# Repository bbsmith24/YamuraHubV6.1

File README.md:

## YamuraLog Hub
Control for YamuraLog sensor network. Start/Stop logging, save log file to microSD, handle FTP communications with data viewer

## Hardware
- Teensy 4.1. Log files go to its built-in microSD slot (4-bit SDIO, `SD.begin(BUILTIN_SDCARD)`), not the display's SD slot.
- Waveshare SN65HVD230 CAN tranciever
- Hosyond 4" 320x480 display (with built in microSD card slot)
- Adafruit Airlift

## Required Libraries
This is a Visual Code/Platform IO project, I don't recommend using Arduino IDE for this, although the code did start there.
Install these libraries:

- `WiFiNINA - Adafruit fork`
- `SPI`
- 'TFT_eSPI'
- 'FlexCan_T4'
- 'ArduinoJson'

## Usage

1. Open `WiFiSecrets.h`.
2. Replace the WiFi credentials:
   - `YOUR_SSID`
   - `YOUR_WIFI_PASSWORD`
3. Replace the FTP server details:
   - `FTP_SERVER`
   - `FTP_USER`
   - `FTP_PASS`
   - 'FTP_PATH'
4. Adjust pin definitions in main.h as needed:
5. Build and upload to Teensy 4.1.
6. For full debug messages, uncomment #define DEBUG_EXTRA_VERBOSE. Use #define DEBUG_VERBOSE for more serious(?) messages
7. Open Serial Monitor at `115200` baud.

## Configuration (SD `config.ini`)

The values in `WiFiSecrets.h` are compiled-in **defaults**. If a `config.ini`
file is present at the top level of the SD card, its fields override those
defaults at boot, and its `[drivers]` section fills the Select Driver menu.
Copy `config.ini.sample` to the card as `config.ini` and edit it. Any field you
omit keeps its compiled default. This keeps real credentials off committed
source. See `Config.h` for the format.

## Notes

- To log anything, you need at least 1 YamuraLog node (GPS, IMU, A/D), appropriate CAN cables and terminators.

## PlatformIO

A `platformio.ini` file is included for Teensy 4.1 builds (`env:teensy41`).

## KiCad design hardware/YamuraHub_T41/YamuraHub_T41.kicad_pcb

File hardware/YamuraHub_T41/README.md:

# YamuraLog Hub carrier board, Teensy 4.1 (rev B)

A 2-layer, all through-hole board, 122 × 68 mm, built in KiCad 10. It carries the same parts as the YamuraHubV6.1 hub, with the Teensy 4.0 replaced by a Teensy 4.1.

**The display goes on the front; every other part goes on the back.**
- **Front:** the 4″ display (MSP4030/4031, 108 × 60.88 mm) plugs into the J4 socket, with its long side along the board. It's held by M3 standoffs at its own four mounting holes (H5–H8).
- **Back:** the Teensy, AirLift, CAN board, power section, connectors and headers.
- **Board size:** the display outline plus a margin at each end for the four corner mounting holes (H1–H4).

| File | Contents |
|---|---|
| `YamuraHub_T41.kicad_pro / .kicad_sch / .kicad_pcb` | KiCad project, schematic and board |
| `YamuraHub.pretty`, `YamuraHub.kicad_sym` | Project footprint (Teensy 4.1) and symbols |
| `fab/YamuraHub_T41_gerbers.zip` | Gerbers and Excellon drill files, ready to upload to a board house |
| `fab/YamuraHub_T41_BOM.csv` | Bill of materials |
| `docs/` | Schematic PDF, 3D renders (top = display side, bottom = parts side) and layer plots |
| `gen/` | Scripts that generate the whole design from `gen/design.py` (see *Regenerating*) |

## Changes from rev A
- **Two DB9 CAN connectors** (J3, J8), wired in parallel, so the CAN bus can pass through the hub.
- **No on-board buttons or LEDs.** The buttons are panel-mounted and connect to J6. The panel LEDs connect to J7, with their 330 Ω resistors (R1/R2) still on the board.
- **The display plugs straight onto the board** (J4 socket on the front) instead of connecting by cable, and everything else moved to the back.
- **Board size:** 122 × 68 mm, up from 120 × 80 mm, with M3 holes at all four corners.

## What changed from the Teensy 4.0 hub
- **The SD card moved to the Teensy 4.1's built-in microSD slot**, which uses the fast 4-bit SDIO interface. The old SD chip select (pin 3) and the display's SD slot are no longer used, and the display's `SD_CS` pin is left unconnected.
- **The display's SDO (MISO) line is cut off by default with JP1.** The display controller doesn't release its SDO line when it isn't selected, so on a shared MISO line it would interfere with the AirLift. The firmware never reads from the display, so leave JP1 open.

## Pin map (from `src/main.h`)
| Function | Teensy pin |
|---|---|
| SPI: MOSI / MISO / SCK | 11 / 12 / 13 (shared by AirLift and display) |
| AirLift: CS / RESET / BUSY | 5 / 6 / 9 |
| Display: CS / DC (RS) / RST | 15 / 2 / 4 |
| CAN3 (FlexCAN_T4FD): CTX3 / CRX3 | 31 / 30 → SN65HVD230 board |
| Buttons (J6): SELECT / UP / DOWN | 16 / 17 / 18 (to GND, internal pull-ups) |
| LEDs (J7, via R1/R2): recording / GPS | 21 / 22 (330 Ω) |
| I2C (Wire2): SDA2 / SCL2 | 25 / 24 → J5, spare for an on-board GPS |

## Power and CAN
- **J1 power input:** 12 V comes in on J1 and passes through D1 (1N5822, reverse-polarity protection) to the +12 V rail. D4 (1.5KE20A TVS diode) clamps voltage spikes on that rail.
- **5 V supply:** U1 (RECOM R-78E5.0-1.0, a 1 A switching regulator) makes +5 V for the Teensy VIN pin, the AirLift VIN pin, the display VCC pin and the display backlight (LED pin).
- **3.3 V supply:** the Teensy's own 3.3 V output powers the CAN board and J5.
- **J3 and J8 (DB9 male, CAN to the nodes), wired identically:**
  - pin 2 = CAN_L
  - pin 7 = CAN_H
  - pins 3 and 6 = GND
  - pin 9 = +12 V to the nodes, through F1 (1.1 A resettable fuse, shared by both connectors)
  - shell = GND
- **Termination:** the Waveshare SN65HVD230 board has a fixed 120 Ω terminator.
  - **One DB9 used:** the hub is one end of the bus, so leave the terminator in place.
  - **Both DB9s used:** the hub sits mid-bus, so remove the terminator from the Waveshare board, and terminate the two far ends of the bus instead.

## Before ordering, check against your actual parts
1. **AirLift (A2), 12-pin socket**, pin order assumed to be VIN, 3Vo, GND, SCK, MISO, MOSI, CS, BUSY, RST, GP0, RXI, TXO.
2. **Waveshare CAN board (A3), 4-pin socket**, pin order assumed to be 3V3, GND, CTX, CRX. Its CANH/CANL terminals connect to J2 with two short wires.
3. **Display (J4)** follows the MSP4030/4031 14-pin header: VCC, GND, LCD_CS, LCD_RST, LCD_RS, SDI, SCK, LED, SDO, CTP ×4, SD_CS.
4. **Display header position:** J4 assumes the display's header is 2.0 mm in from its left short edge, centred vertically (13.93 mm from top and bottom), with pin 1 (VCC) nearest the bottom edge, front view. These figures come from the MSP4030/4031 outline drawing. Measure your display before ordering; if they're off, the display won't line up with H5–H8.

Each socket's signal names are printed on the silkscreen. If a module's order differs, edit `pins` and `pinnames` for that part in `gen/design.py` and regenerate.

## Assembly notes
- **Cut the Teensy's VUSB-VIN pad** on its underside. Otherwise, with USB plugged in, USB and the board's 5 V supply are tied together.
- **Back-side parts:** solder every part except J4 on the back of the board. Mount the Teensy on female headers, with its USB port at the top edge and its microSD slot at the bottom edge so the card can be swapped.
- **Trim leads under the display:** cut the back-side parts' leads flush on the front. The display's underside (SMD parts up to 2.2 mm, plus its SD slot) sits over them, held at the J4 socket height by the standoffs.
- **Leave JP1 open** (see above).
- **Panel controls:** J6 (SELECT, UP, DOWN, GND) and J7 (REC, GPS, GND) go to the panel buttons and LEDs.

## Firmware
The `teensy41` branch of YamuraHubV6.1 already builds for this board: `env:teensy41`, with `SD.begin(BUILTIN_SDCARD)`. Every other pin is unchanged from the Teensy 4.0 hub.

## Regenerating
Everything in this folder is generated from `gen/design.py`:
```
python gen/build_sch.py                                      # schematic and symbol library
kicad-cli sch export netlist -o gen/out/YamuraHub_T41.net YamuraHub_T41.kicad_sch
"C:/Program Files/KiCad/10.0/bin/python.exe" gen/build_pcb.py  # placement; pad nets come from the netlist
"C:/Program Files/KiCad/10.0/bin/python.exe" gen/route.py      # grid router and GND pours
```
- **Back-side parts:** parts marked `side="B"` in `design.py` are flipped onto the back, and their labels go on the back silkscreen.
- **Routing retries:** the router routes one net at a time. If a net fails, it starts again with the failed nets routed first, for up to 8 attempts.
- **Hand edits:** rebuilding this way discards any hand edits made in KiCad. If you route by hand in KiCad, stop running these scripts.

## Check results (rev B)
- **ERC:** 0 errors, 0 warnings.
- **DRC with schematic parity:** 0 unconnected pads, 0 board/schematic mismatches, and no courtyard or clearance errors.
- **Remaining DRC warnings, not errors:** two ground-pour connections are partial thermal reliefs. Both pads are also connected by tracks.

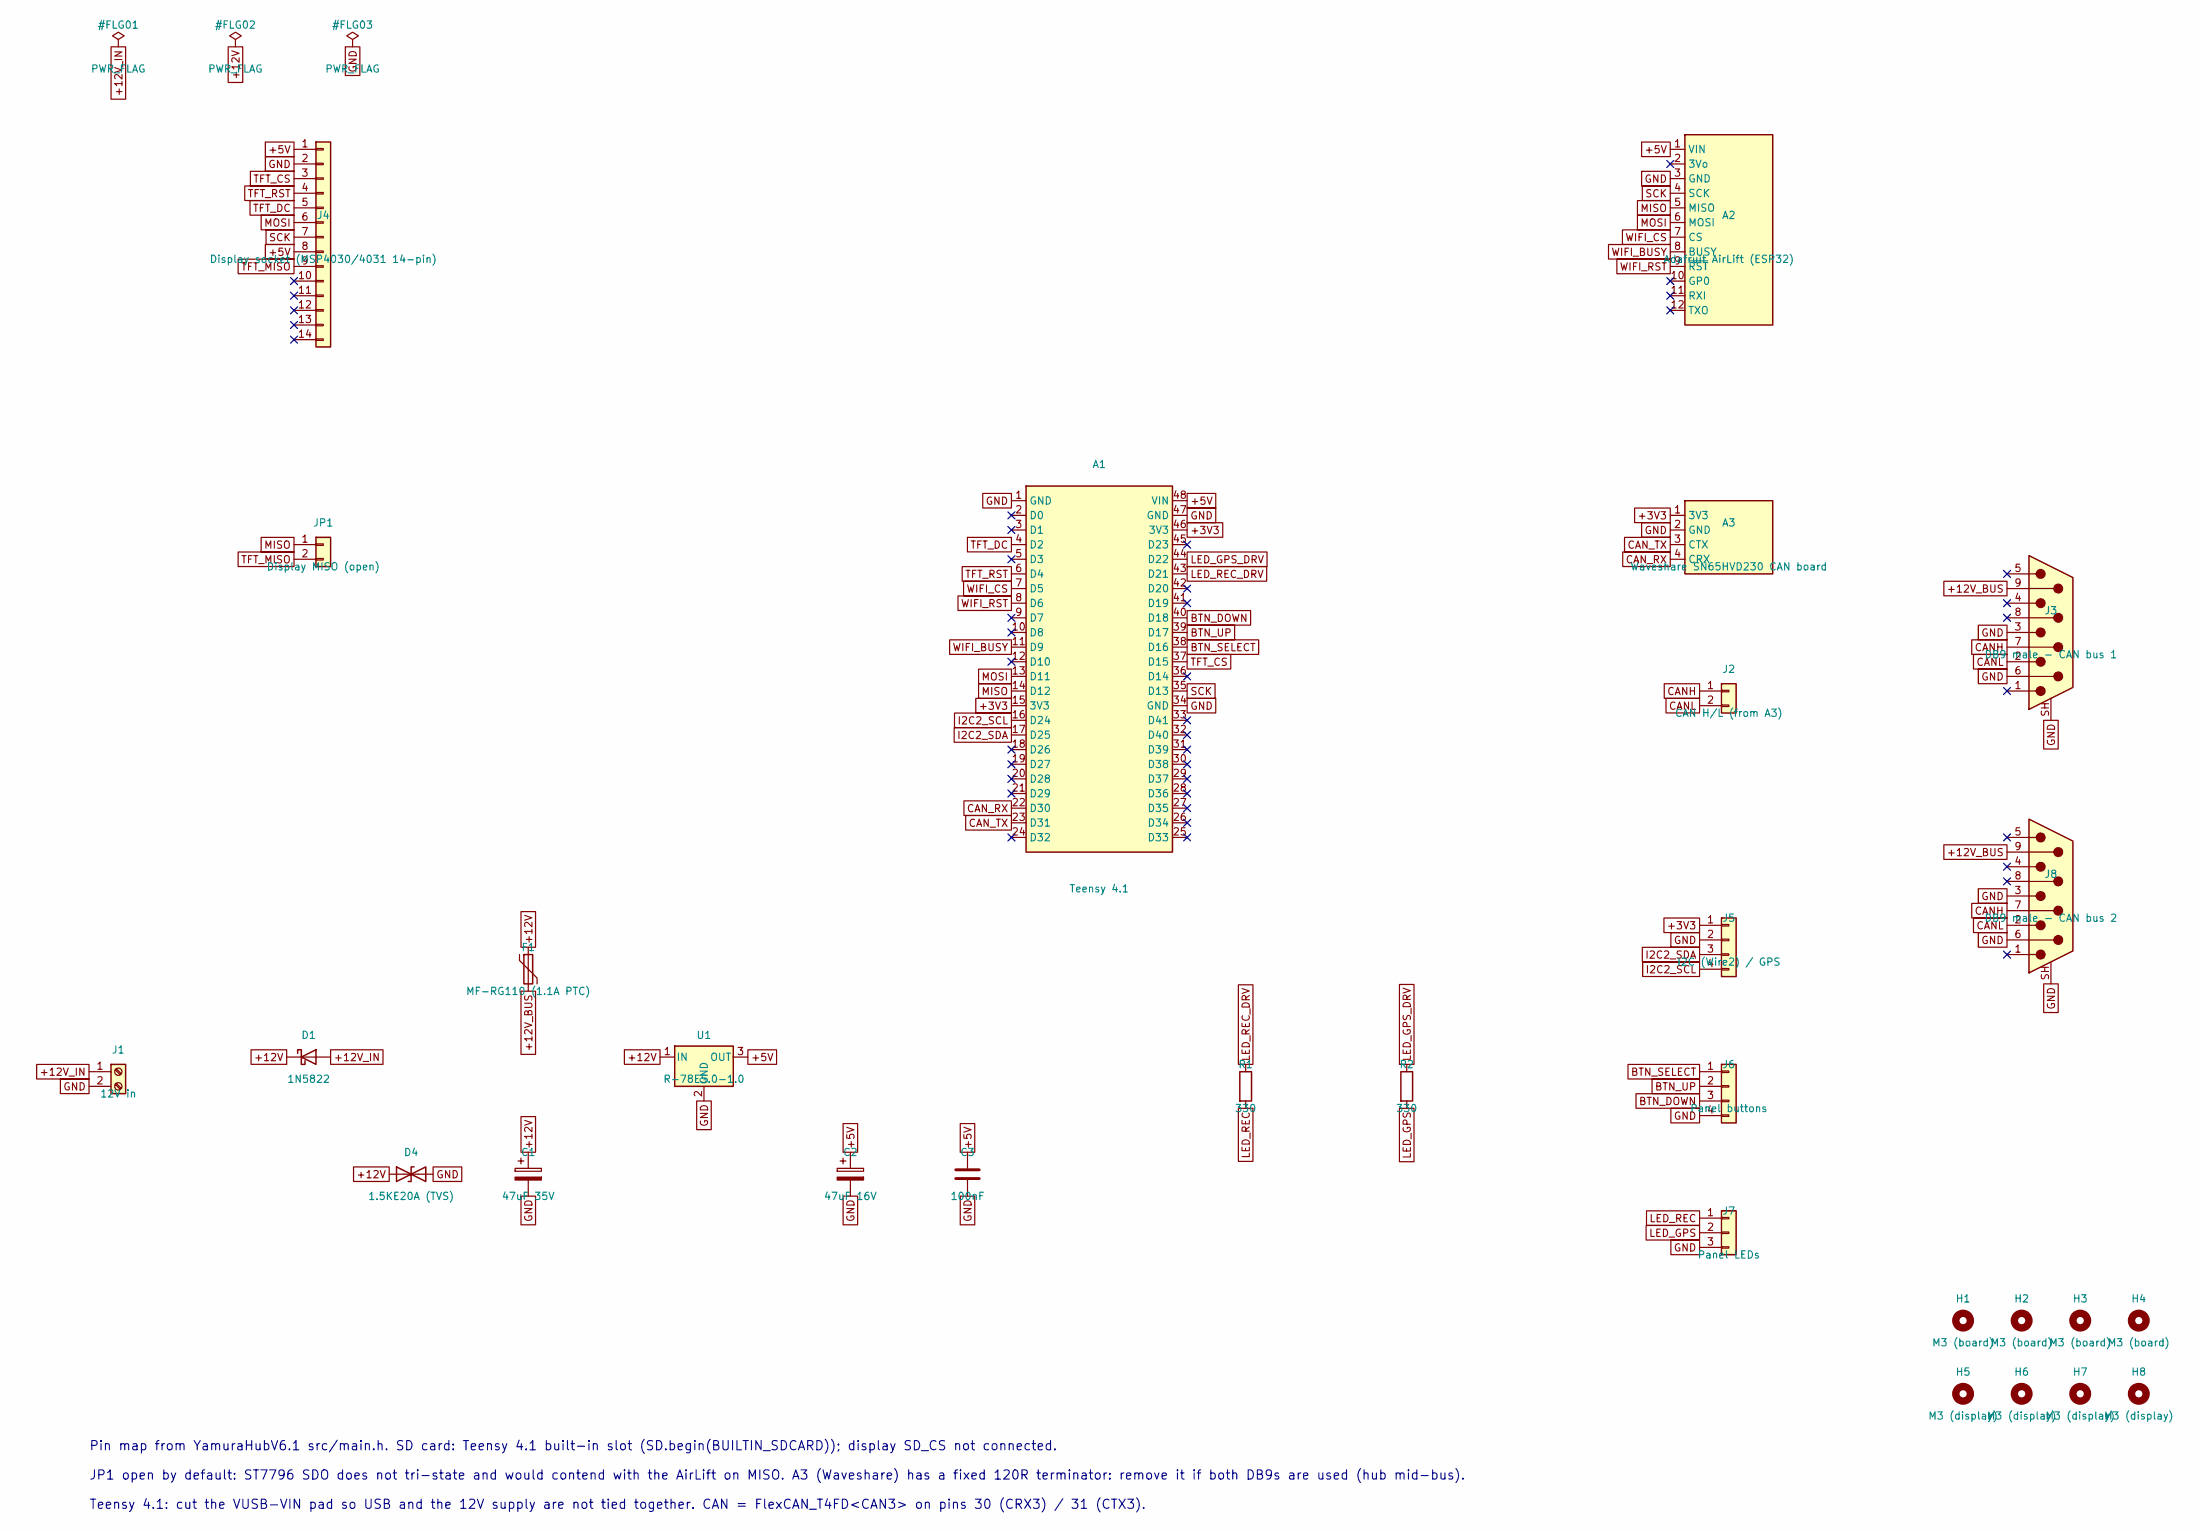
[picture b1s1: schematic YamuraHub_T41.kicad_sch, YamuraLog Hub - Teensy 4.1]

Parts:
A1: Teensy 4.1; Teensy41
A2: Adafruit AirLift (ESP32); PinSocket_1x12_P2.54mm_Vertical
A3: Waveshare SN65HVD230 CAN board; PinSocket_1x04_P2.54mm_Vertical
C1: 47uF 35V; CP_Radial_D8.0mm_P3.50mm
C2: 47uF 16V; CP_Radial_D8.0mm_P3.50mm
C3: 100nF; C_Disc_D5.0mm_W2.5mm_P5.00mm
D1: 1N5822; D_DO-201AD_P15.24mm_Horizontal
D4: 1.5KE20A (TVS); D_DO-201AE_P5.08mm_Vertical_CathodeUp
F1: MF-RG110 (1.1A PTC); Fuse_Bourns_MF-RG1100
H1, H2, H3, H4: M3 (board); MountingHole_3.2mm_M3
H5, H6, H7, H8: M3 (display); MountingHole_3.2mm_M3
J1: 12V in; TerminalBlock_Phoenix_MKDS-1,5-2-5.08_1x02_P5.08mm_Horizont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
J2: CAN H/L (from A3); PinHeader_1x02_P2.54mm_Vertical
J3: DB9 male - CAN bus 1; DSUB-9_Pins_Horizontal_P2.77x2.84mm_EdgePinOffset7.70mm_Hou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
J4: Display socket (MSP4030/4031 14-pin); PinSocket_1x14_P2.54mm_Vertical
J5: I2C (Wire2) / GPS; PinHeader_1x04_P2.54mm_Vertical
J6: Panel buttons; PinHeader_1x04_P2.54mm_Vertical
J7: Panel LEDs; PinHeader_1x03_P2.54mm_Vertical
J8: DB9 male - CAN bus 2; DSUB-9_Pins_Horizontal_P2.77x2.84mm_EdgePinOffset7.70mm_Hou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
JP1: Display MISO (open); PinHeader_1x02_P2.54mm_Vertical
R1, R2: 330; R_Axial_DIN0207_L6.3mm_D2.5mm_P10.16mm_Horizontal
U1: R-78E5.0-1.0; Converter_DCDC_RECOM_R-78E-0.5_THT

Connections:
+3V3: A1.15 (3V3), A1.46 (3V3), A3.1 (3V3), J5.1
+5V: A1.48 (VIN), A2.1 (VIN), C2.1, C3.1, J4.1, J4.8, U1.3 (OUT)
+12V: C1.1, D1.1 (K), D4.1 (A1), F1.1, U1.1 (IN)
+12V_BUS: F1.2, J3.9, J8.9
+12V_IN: D1.2 (A), J1.1
BTN_DOWN: A1.40 (D18), J6.3
BTN_SELECT: A1.38 (D16), J6.1
BTN_UP: A1.39 (D17), J6.2
CANH: J2.1, J3.7, J8.7
CANL: J2.2, J3.2, J8.2
CAN_RX: A1.22 (D30), A3.4 (CRX)
CAN_TX: A1.23 (D31), A3.3 (CTX)
GND: A1.1 (GND), A1.34 (GND), A1.47 (GND), A2.3 (GND), A3.2 (GND), C1.2, C2.2, C3.2, D4.2 (A2), J1.2, J3.3, J3.6, J3.SH (PAD), J4.2, J5.2, J6.4, J7.3, J8.3, J8.6, J8.SH (PAD), U1.2 (GND)
I2C2_SCL: A1.16 (D24), J5.4
I2C2_SDA: A1.17 (D25), J5.3
LED_GPS: J7.2, R2.2
LED_GPS_DRV: A1.44 (D22), R2.1
LED_REC: J7.1, R1.2
LED_REC_DRV: A1.43 (D21), R1.1
MISO: A1.14 (D12), A2.5 (MISO), JP1.1
MOSI: A1.13 (D11), A2.6 (MOSI), J4.6
SCK: A1.35 (D13), A2.4 (SCK), J4.7
TFT_CS: A1.37 (D15), J4.3
TFT_DC: A1.4 (D2), J4.5
TFT_MISO: J4.9, JP1.2
TFT_RST: A1.6 (D4), J4.4
WIFI_BUSY: A1.11 (D9), A2.8 (BUSY)
WIFI_CS: A1.7 (D5), A2.7 (CS)
WIFI_RST: A1.8 (D6), A2.9 (~RST)

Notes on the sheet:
Pin map from YamuraHubV6.1 src/main.h. SD card: Teensy 4.1 built-in slot (SD.begin(BUILTIN_SDCARD)); display SD_CS not connected.
JP1 open by default: ST7796 SDO does not tri-state and would contend with the AirLift on MISO. A3 (Waveshare) has a fixed 120R terminator: remove it if both DB9s are used (hub mid-bus).
Teensy 4.1: cut the VUSB-VIN pad so USB and the 12V supply are not tied together. CAN = FlexCAN_T4FD<CAN3> on pins 30 (CRX3) / 31 (CTX3).

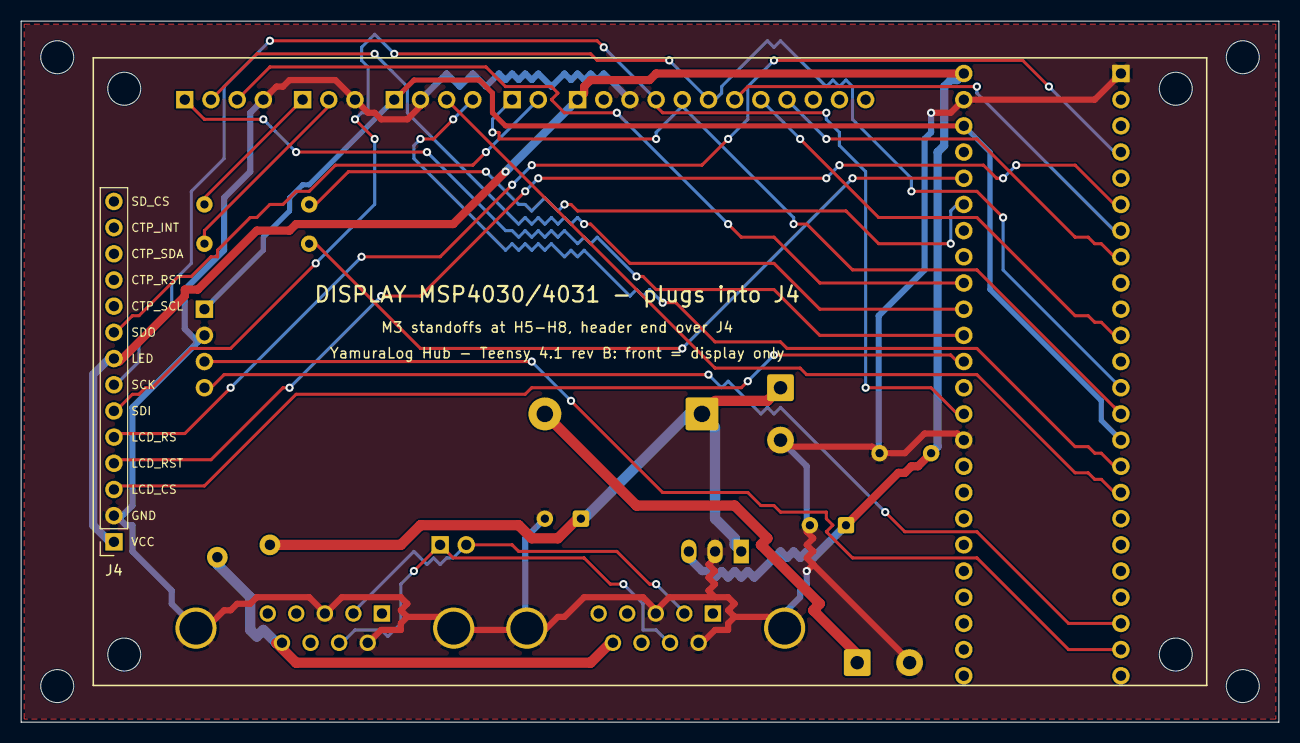
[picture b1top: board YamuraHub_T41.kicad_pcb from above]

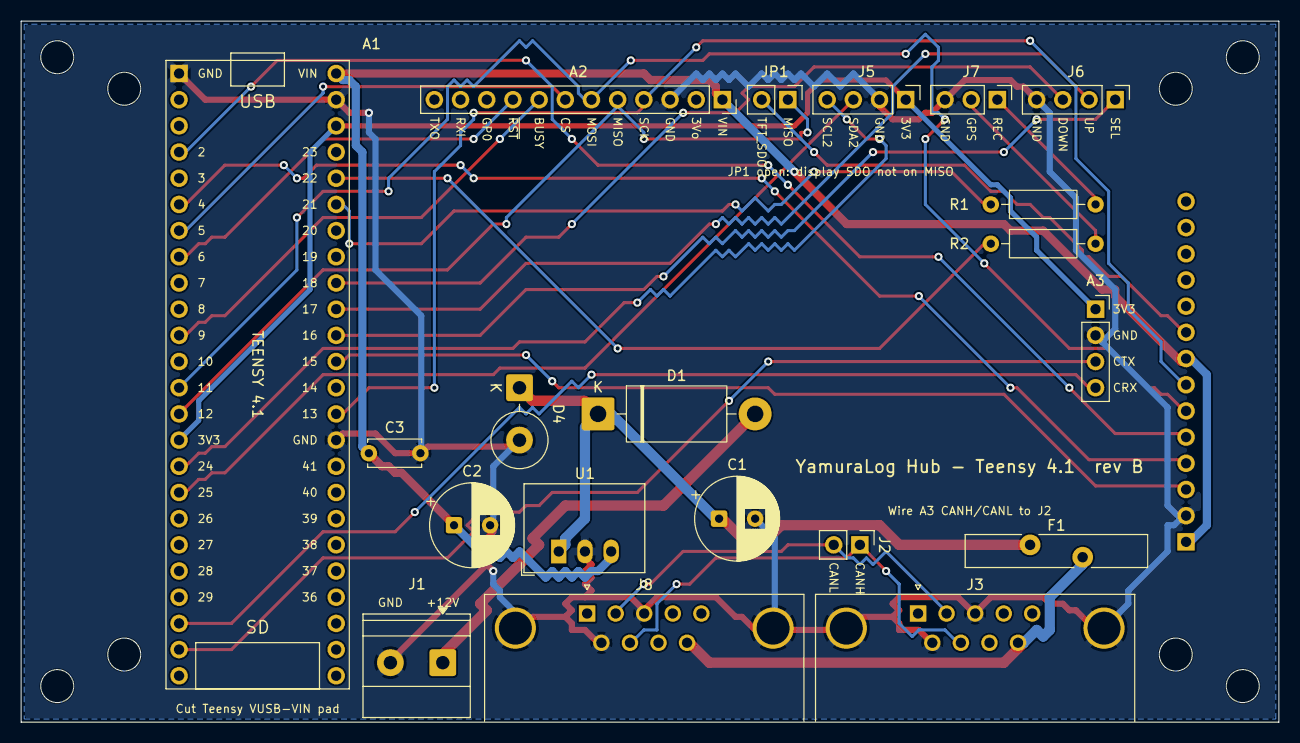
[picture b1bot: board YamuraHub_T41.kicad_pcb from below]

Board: 2 copper layers, 122.0 x 68.0 mm, 29 parts (20 on the bottom side), 29 nets.

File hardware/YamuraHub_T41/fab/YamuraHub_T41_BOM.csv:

"Reference","Value","Footprint","QUANTITY"
"A1","Teensy 4.1","YamuraHub:Teensy41","1"
"A2","Adafruit AirLift (ESP32)","Connector_PinSocket_2.54mm:PinSocket_1x12_P2.54mm_Vertical","1"
"A3","Waveshare SN65HVD230 CAN board","Connector_PinSocket_2.54mm:PinSocket_1x04_P2.54mm_Vertical","1"
"C1","47uF 35V","Capacitor_THT:CP_Radial_D8.0mm_P3.50mm","1"
"C2","47uF 16V","Capacitor_THT:CP_Radial_D8.0mm_P3.50mm","1"
"C3","100nF","Capacitor_THT:C_Disc_D5.0mm_W2.5mm_P5.00mm","1"
"D1","1N5822","Diode_THT:D_DO-201AD_P15.24mm_Horizontal","1"
"D4","1.5KE20A (TVS)","Diode_THT:D_DO-201AE_P5.08mm_Vertical_CathodeUp","1"
"F1","MF-RG110 (1.1A PTC)","Fuse:Fuse_Bourns_MF-RG1100","1"
"J1","12V in","TerminalBlock_Phoenix:TerminalBlock_Phoenix_MKDS-1,5-2-5.08_1x02_P5.08mm_Horizontal","1"
"J2","CAN H/L (from A3)","Connector_PinHeader_2.54mm:PinHeader_1x02_P2.54mm_Vertical","1"
"J3","DB9 male - CAN bus 1","Connector_Dsub:DSUB-9_Pins_Horizontal_P2.77x2.84mm_EdgePinOffset7.70mm_Housed_MountingHolesOffset9.12mm","1"
"J4","Display socket (MSP4030/4031 14-pin)","Connector_PinSocket_2.54mm:PinSocket_1x14_P2.54mm_Vertical","1"
"J5","I2C (Wire2) / GPS","Connector_PinHeader_2.54mm:PinHeader_1x04_P2.54mm_Vertical","1"
"J6","Panel buttons","Connector_PinHeader_2.54mm:PinHeader_1x04_P2.54mm_Vertical","1"
"J7","Panel LEDs","Connector_PinHeader_2.54mm:PinHeader_1x03_P2.54mm_Vertical","1"
"J8","DB9 male - CAN bus 2","Connector_Dsub:DSUB-9_Pins_Horizontal_P2.77x2.84mm_EdgePinOffset7.70mm_Housed_MountingHolesOffset9.12mm","1"
"JP1","Display MISO (open)","Connector_PinHeader_2.54mm:PinHeader_1x02_P2.54mm_Vertical","1"
"R1,R2","330","Resistor_THT:R_Axial_DIN0207_L6.3mm_D2.5mm_P10.16mm_Horizontal","2"
"U1","R-78E5.0-1.0","Converter_DCDC:Converter_DCDC_RECOM_R-78E-0.5_THT","1"

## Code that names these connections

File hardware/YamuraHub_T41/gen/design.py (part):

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DISP_HDR_X, DISP_HDR_PIN1_Y = DISP_X0 + 2.0, DISP_Y0 + 13.93 + 33.02
CORNER_HOLES = [(3.5, 3.5), (BOARD_W - 3.5, 3.5), (3.5, BOARD_H - 3.5), (BOARD_W - 3.5, BOARD_H - 3.5)]
DB9_Y = BOARD_H - 10.54                  # DB9 flange flush with bottom edge
DB9_PINS = {"2": "CANL", "7": "CANH", "3": "GND", "6": "GND", "9": "+12V_BUS", "SH": "GND"}
DB9_FP = "Connector_Dsub:DSUB-9_Pins_Horizontal_P2.77x2.84mm_EdgePinOffset7.70mm_Housed_MountingHolesOffset9.12mm"

PARTS = [
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         ref_pos=(88.0, 2.2), sym="local:Teensy41", pins=teensy_pinnets),
    dict(ref="A2", value="Adafruit AirLift (ESP32)", fp="Connector_PinSocket_2.54mm:PinSocket_1x12_P2.54mm_Vertical",
         pos=(53.975, 7.62), rot=-90, side="B", ref_pos=(67.945, 4.9), sym="local:AirLift",
         pins={"1": "+5V", "3": "GND", "4": "SCK", "5": "MISO", "6": "MOSI", "7": "WIFI_CS",
               "8": "WIFI_BUSY", "9": "WIFI_RST"},
         pinnames=["VIN", "3Vo", "GND", "SCK", "MISO", "MOSI", "CS", "BUSY", "~{RST}", "GP0", "RXI", "TXO"]),
    dict(ref="A3", value="Waveshare SN65HVD230 CAN board", fp="Connector_PinSocket_2.54mm:PinSocket_1x04_P2.54mm_Vertical",
         pos=(17.78, 27.94), rot=0, side="B", sym="local:CANBoard",
         pins={"1": "+3V3", "2": "GND", "3": "CAN_TX", "4": "CAN_RX"},
         pinnames=["3V3", "GND", "CTX", "CRX"]),
    dict(ref="J2", value="CAN H/L (from A3)", fp="Connector_PinHeader_2.54mm:PinHeader_1x02_P2.54mm_Vertical",
         pos=(40.64, 50.8), rot=-90, side="B", sym="Connector_Generic:Conn_01x02",
         pins={"1": "CANH", "2": "CANL"}, pinnames=["CANH", "CANL"]),
    dict(ref="J3", value="DB9 male - CAN bus 1", fp=DB9_FP, pos=(35.0, DB9_Y), rot=0, side="B",
         sym="Connector:DE9_Pins_MountingHoles", pins=DB9_PINS),
    dict(ref="J8", value="DB9 male - CAN bus 2", fp=DB9_FP, pos=(67.1, DB9_Y), rot=0, side="B",
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         pins={"1": "+5V", "2": "GND"}),
    dict(ref="J4", value="Display socket (MSP4030/4031 14-pin)", fp="Connector_PinSocket_2.54mm:PinSocket_1x14_P2.54mm_Vertical",
         pos=(DISP_HDR_X, DISP_HDR_PIN1_Y), rot=180, side="F", sym="Connector_Generic:Conn_01x14",
         pins={"1": "+5V", "2": "GND", "3": "TFT_CS", "4": "TFT_RST", "5": "TFT_DC", "6": "MOSI",
               "7": "SCK", "8": "+5V", "9": "TFT_MISO"},
         pinnames=["VCC", "GND", "LCD_CS", "LCD_RST", "LCD_RS", "SDI", "SCK", "LED", "SDO",
                   "CTP_SCL", "CTP_RST", "CTP_SDA", "CTP_INT", "SD_CS"], label_side="right"),
    dict(ref="JP1", value="Display MISO (open)", fp="Connector_PinHeader_2.54mm:PinHeader_1x02_P2.54mm_Vertical",
         pos=(47.625, 7.62), rot=-90, side="B", ref_pos=(48.895, 4.9), sym="Connector_Generic:Conn_01x02",
         pins={"1": "MISO", "2": "TFT_MISO"}, pinnames=["MISO", "TFT_SDO"]),
    dict(ref="J5", value="I2C (Wire2) / GPS", fp="Connector_PinHeader_2.54mm:PinHeader_1x04_P2.54mm_Vertical",
         pos=(36.195, 7.62), rot=-90, side="B", ref_pos=(40.005, 4.9), sym="Connector_Generic:Conn_01x04",
         pins={"1": "+3V3", "2": "GND", "3": "I2C2_SDA", "4": "I2C2_SCL"},
         pinnames=["3V3", "GND", "SDA2", "SCL2"]),
    dict(ref="J6", value="Panel buttons", fp="Connector_PinHeader_2.54mm:PinHeader_1x04_P2.54mm_Vertical",
         pos=(15.875, 7.62), rot=-90, side="B", ref_pos=(19.685, 4.9), sym="Connector_Generic:Conn_01x04",
         pins={"1": "BTN_SELECT", "2": "BTN_UP", "3": "BTN_DOWN", "4": "GND"},
         pinnames=["SEL", "UP", "DOWN", "GND"]),
    dict(ref="J7", value="Panel LEDs", fp="Connector_PinHeader_2.54mm:PinHeader_1x03_P2.54mm_Vertical",
         pos=(27.305, 7.62), rot=-90, side="B", ref_pos=(29.845, 4.9), sym="Connector_Generic:Conn_01x03",
         pins={"1": "LED_REC", "2": "LED_GPS", "3": "GND"},
         pinnames=["REC", "GPS", "GND"]),
    dict(ref="R1", value="330", fp="Resistor_THT:R_Axial_DIN0207_L6.3mm_D2.5mm_P10.16mm_Horizontal",
         pos=(27.94, 17.78), rot=0, side="B", ref_pos=(31.0, 17.78), sym="Device:R", pins={"1": "LED_REC_DRV", "2": "LED_REC"}),
    dict(ref="R2", value="330", fp="Resistor_THT:R_Axial_DIN0207_L6.3mm_D2.5mm_P10.16mm_Horizontal",
         pos=(27.94, 21.59), rot=0, side="B", ref_pos=(31.0, 21.59), sym="Device:R", pins={"1": "LED_GPS_DRV", "2": "LED_GPS"}),
] + [dict(ref=f"H{i+1}", value="M3 (board)", hide_ref=True, fp="MountingHole:MountingHole_3.2mm_M3", pos=xy, rot=0,
          side="F", sym="Mechanical:MountingHole", pins={}) for i, xy in enumerate(CORNER_HOLES)] \
  + [dict(ref=f"H{i+5}", value="M3 (display)", hide_ref=True, fp="MountingHole:MountingHole_3.2mm_M3", pos=xy, rot=0,
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
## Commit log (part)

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2026-05-10 Added header
    Added header in main.cpp. Initial checking of locally implemented FTPClient, Teensy 4.0 + Airlift + ESP32 TFT display with built in microSD card. Might be possible to add Airlift functionality to the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
    Broke TFT menu system out into it's own (at this point partially complete...) class
2026-06-12 recent changes
    recent changes
